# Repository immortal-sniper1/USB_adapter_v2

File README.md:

# USB_adapter_v2
 usb to uart adaptor v2

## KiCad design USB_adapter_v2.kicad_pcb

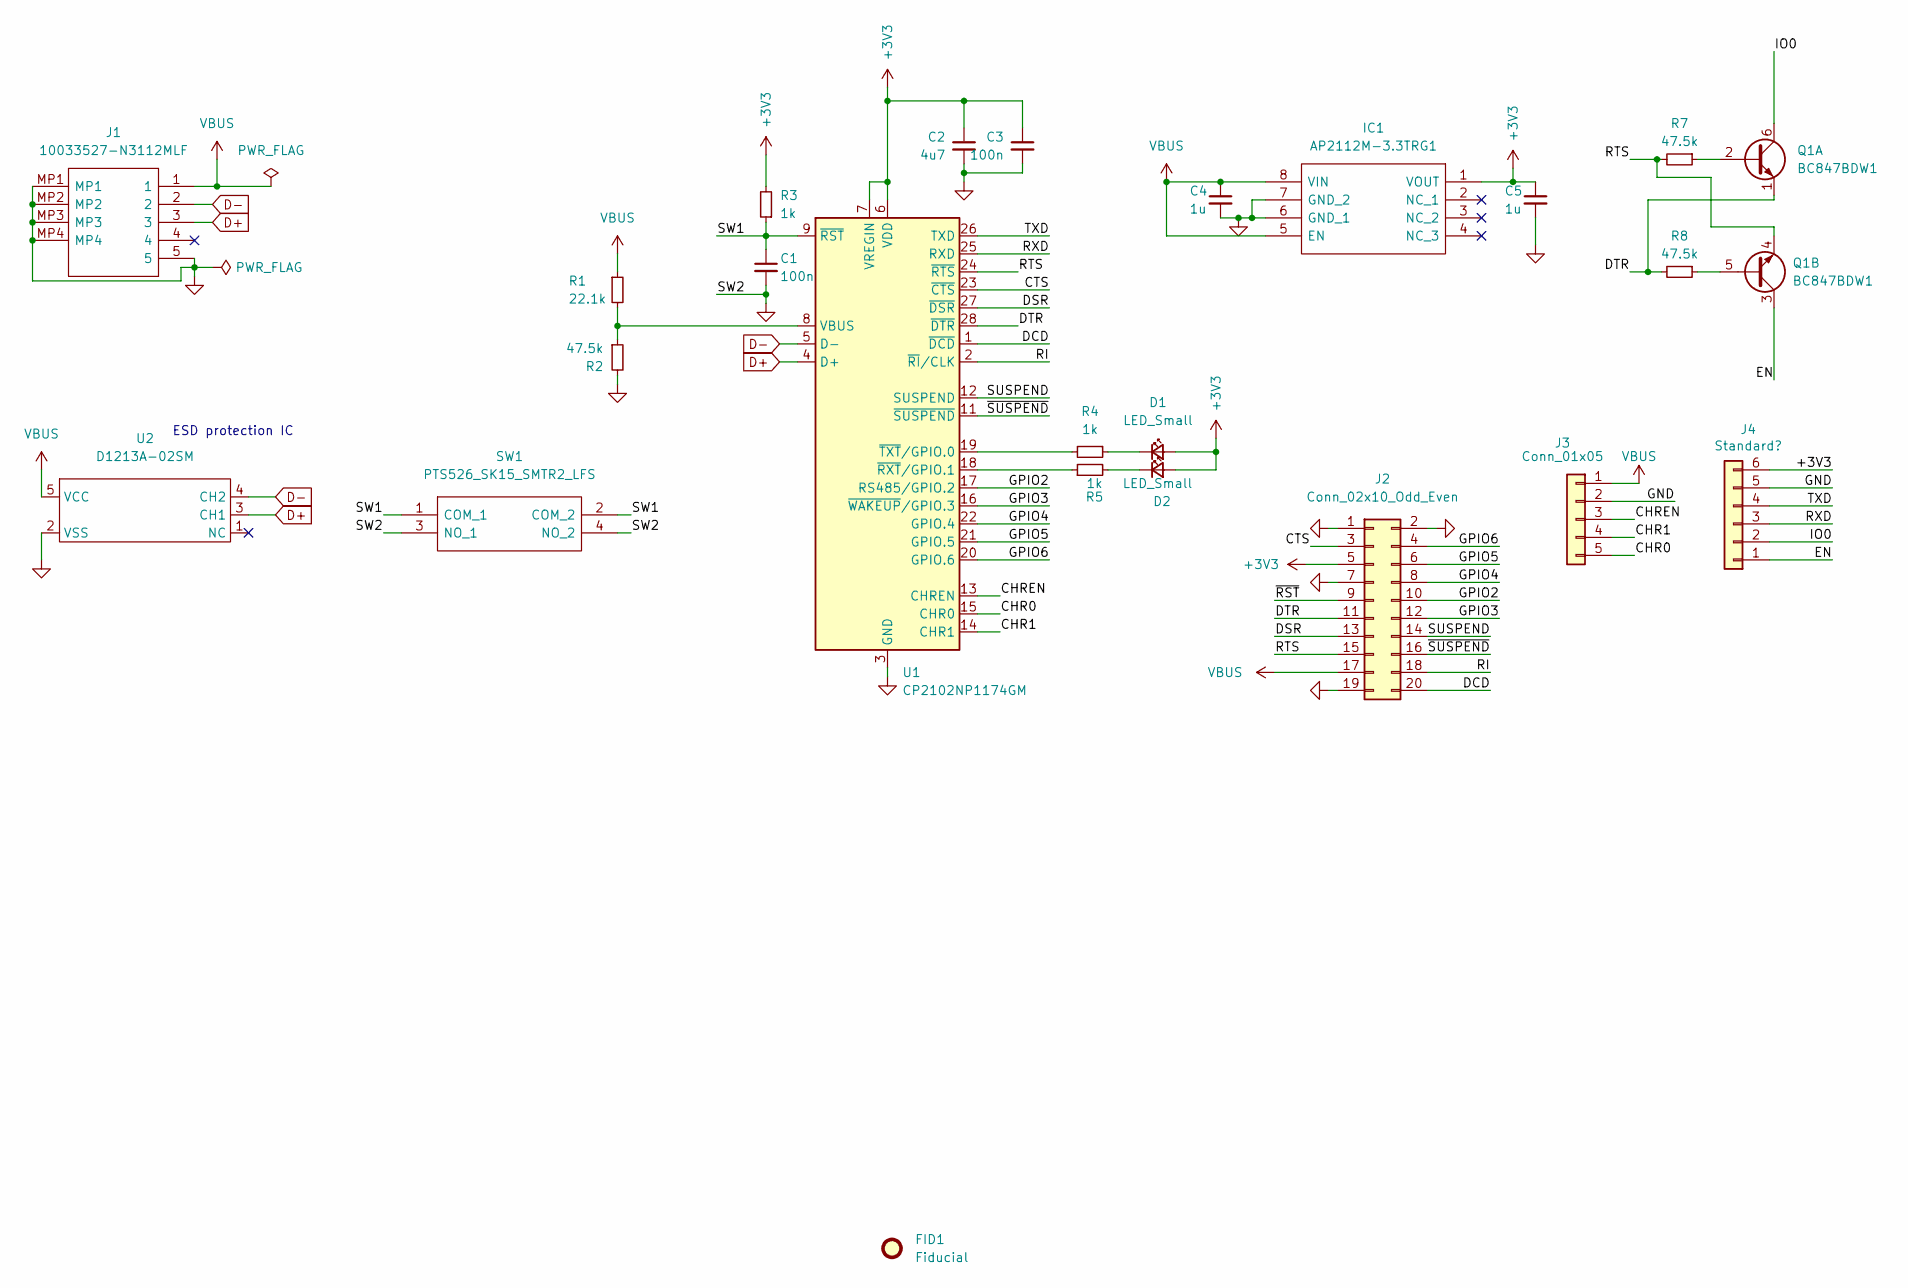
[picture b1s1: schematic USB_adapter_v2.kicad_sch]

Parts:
C1, C3: 100n; C_0603_1608Metric_Pad1.08x0.95mm_HandSolder
C2: 4u7; C_0603_1608Metric_Pad1.08x0.95mm_HandSolder
C4, C5: 1u; C_0603_1608Metric_Pad1.08x0.95mm_HandSolder
D1, D2: LED_Small; LED_0603_1608Metric_Pad1.05x0.95mm_HandSolder
FID1: Fiducial; Fiducial_0.75mm_Mask1.5mm
IC1: AP2112M-3.3TRG1; SOIC127P600X170-8N; Mouser Part Number 621-AP2112M-3.3TRG1
J1: 10033527-N3112MLF; 10033527N3112MLF; Mouser Part Number 649-10033527N3112MLF
J2: Conn_02x10_Odd_Even; PinHeader_2x10_P2.54mm_Vertical
J3: Conn_01x05; PinHeader_1x05_P2.54mm_Vertical
J4: Standard?; PinHeader_1x06_P2.54mm_Vertical
Q1: BC847BDW1; SOT-363_SC-70-6
R1: 22.1k; R_0603_1608Metric_Pad0.98x0.95mm_HandSolder
R2, R7, R8: 47.5k; R_0603_1608Metric_Pad0.98x0.95mm_HandSolder
R3, R4, R5: 1k; R_0603_1608Metric_Pad0.98x0.95mm_HandSolder
SW1: PTS526_SK15_SMTR2_LFS; PTS526SK15SMTR2LFS; Mouser Part Number 611-PTS526SK15SMR2L
U1: CP2102NP1174GM; QFN-28-1EP_5x5mm_P0.5mm_EP3.35x3.35mm
U2: D1213A-02SM; SOT-23-5_HandSoldering

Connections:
+3V3: C2.1, C3.1, C5.1, D1.2 (A), D2.2 (A), IC1.1 (VOUT), J2.5, J4.6, R3.2, U1.6 (VDD), U1.7 (VREGIN)
/CHR0: J3.5, U1.15 (CHR0)
/CHR1: J3.4, U1.14 (CHR1)
/CHREN: J3.3, U1.13 (CHREN)
/CTS: J2.3, U1.23 (~CTS)
/DCD: J2.20, U1.1 (~DCD)
/DSR: J2.13, U1.27 (~DSR)
/DTR: J2.11, Q1.1 (E1), R8.2, U1.28 (~DTR)
/EN: J4.1, Q1.3 (C2)
/GPIO2: J2.10, U1.17 (RS485/GPIO.2)
/GPIO3: J2.12, U1.16 (~WAKEUP/GPIO.3)
/GPIO4: J2.8, U1.22 (GPIO.4)
/GPIO5: J2.6, U1.21 (GPIO.5)
/GPIO6: J2.4, U1.20 (GPIO.6)
/IO0: J4.2, Q1.6 (C1)
/RI: J2.18, U1.2 (~RI/CLK)
/RTS: J2.15, Q1.4 (E2), R7.2, U1.24 (~RTS)
/RXD: J4.3, U1.25 (RXD)
/SUSPEND: J2.14, U1.12 (SUSPEND)
/SW1: C1.1, R3.1, SW1.1 (COM_1), SW1.2 (COM_2), U1.9 (~RST)
/TXD: J4.4, U1.26 (TXD)
/~RST: J2.9
/~SUSPEND: J2.16, U1.11 (~SUSPEND)
D+: J1.3, U1.4 (D+), U2.3 (CH1)
D-: J1.2, U1.5 (D-), U2.4 (CH2)
GND: C1.2, C2.2, C3.2, C4.2, C5.2, IC1.6 (GND_1), IC1.7 (GND_2), J1.5, J1.MP1, J1.MP2, J1.MP3, J1.MP4, J2.1, J2.2, J2.7, J2.19, J3.2, J4.5, R2.2, SW1.3 (NO_1), SW1.4 (NO_2), U1.3 (GND), U1.29 (GND), U2.2 (VSS)
unnamed: D1.1 (K), R4.1
unnamed: D2.1 (K), R5.2
unnamed: Q1.2 (B1), R7.1
unnamed: Q1.5 (B2), R8.1
unnamed: R1.2, R2.1, U1.8 (VBUS)
unnamed: R4.2, U1.19 (~TXT/GPIO.0)
unnamed: R5.1, U1.18 (~RXT/GPIO.1)
VBUS: C4.1, IC1.5 (EN), IC1.8 (VIN), J1.1, J2.17, J3.1, R1.1, U2.5 (VCC)

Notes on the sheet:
ESD protection IC

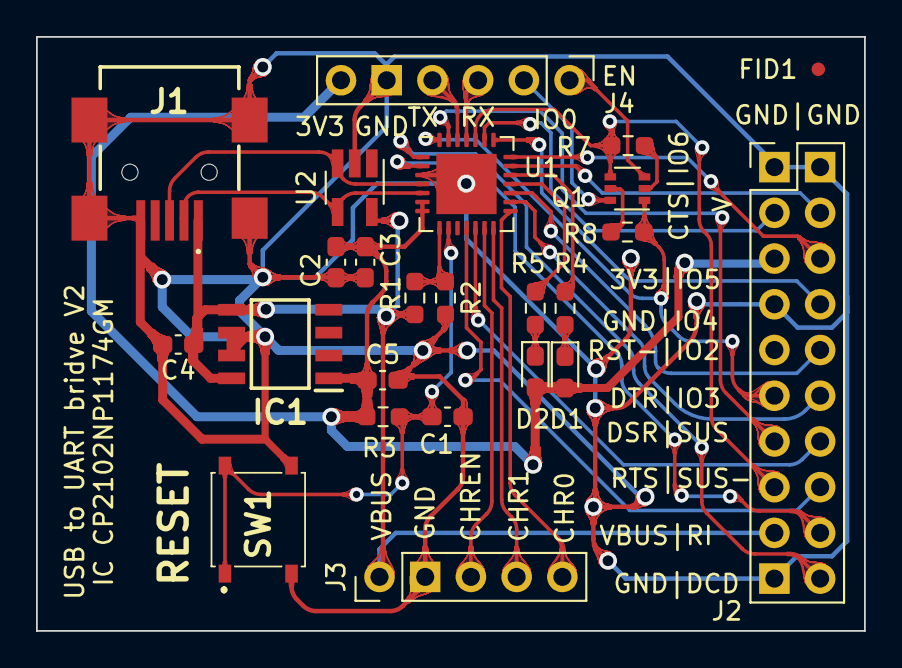
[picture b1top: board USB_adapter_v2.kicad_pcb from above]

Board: 2 copper layers, 46.0 x 33.0 mm, 24 parts (0 on the bottom side), 33 nets.

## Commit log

2022-05-06 succes!
